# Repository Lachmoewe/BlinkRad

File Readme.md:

# BlinkRad

Using old or broken bicycle rims as an ilumination project.

36 boards, 36 rgb-LEDs, 36 attiny13, 108 FETs, 108 resistors 
(at least if youve got 36 spoke rims).
1 controller of your choice.

## Current Status

Got the current version (as of this commit) of boards at home.
Already got one working with 24bit RGB PWM. Now Im trying
to build a useful and robust data protocol. I was thinking
about sending packages with 4bit per color, a used bit and a 
sync bit, adding up to 14bit packages.

## Further plans
- network control with teensy3.1
- develop a protocol to send to attinys
- maybe 433MHz control
- you name it!

## Getting the code to work
You will need the following packages:
```
sudo apt-get install avr-libc binutils-avr gcc-avr avrdude libusb-dev
```

## Pretty Pictures

## Notes
If you want to edit the board, go with either Cadsoft Eagle or
edit the .brd files manually, its only xml.

Thanks to apmorton for creating the teensy template:
https://github.com/apmorton/teensy-template

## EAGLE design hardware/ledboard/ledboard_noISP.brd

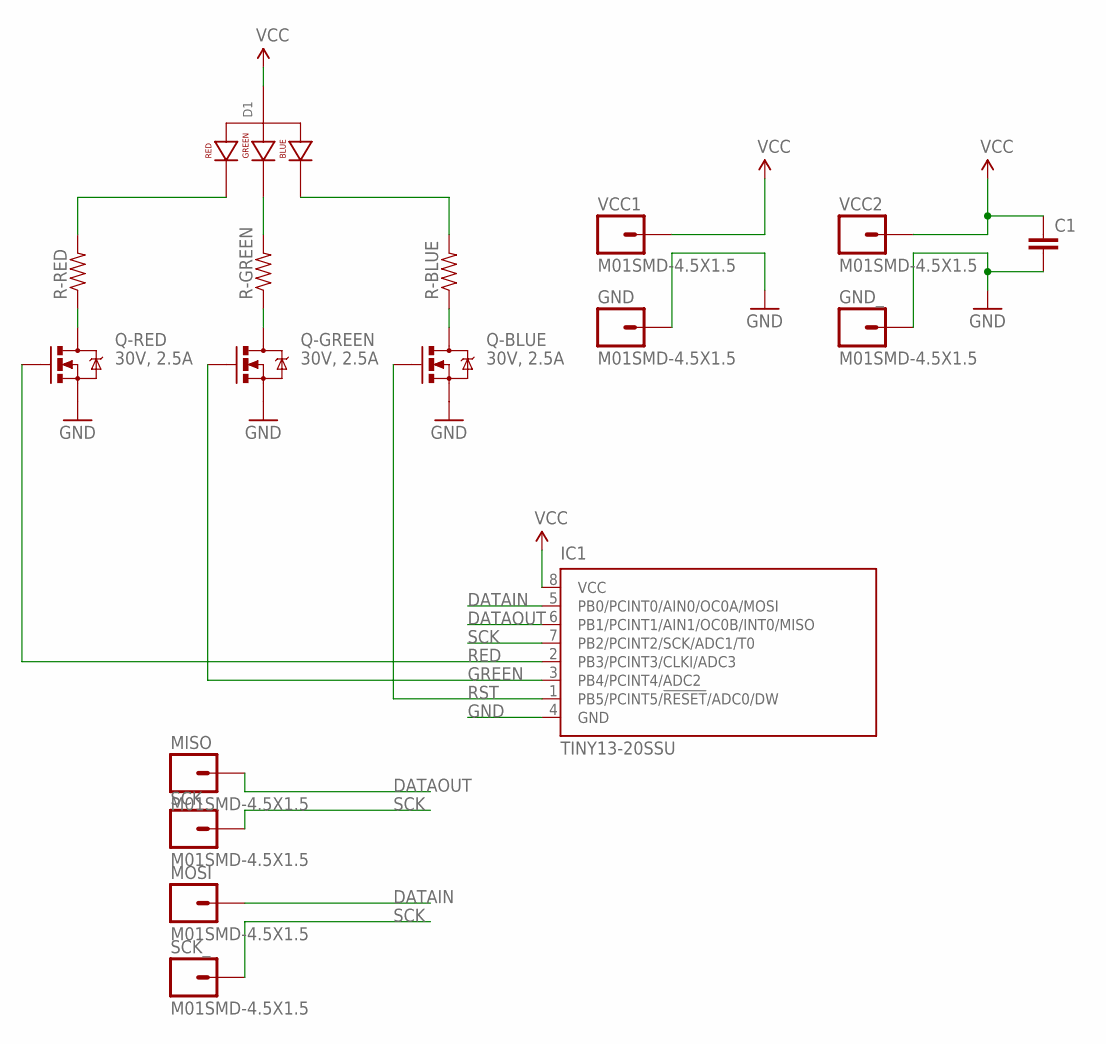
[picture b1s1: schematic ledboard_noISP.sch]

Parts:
C1: CAP0805; 0805
D1: LED-RGB-CA-THRUCLEAR; LED-RGB-THRU
GND: M01SMD-4.5X1.5; PAD-1.5X4.5
GND_: M01SMD-4.5X1.5; PAD-1.5X4.5
IC1: TINY13-20SSU; 8S1
MISO: M01SMD-4.5X1.5; PAD-1.5X4.5
MOSI: M01SMD-4.5X1.5; PAD-1.5X4.5
Q-BLUE: 30V, 2.5A; SOT23
Q-GREEN: 30V, 2.5A; SOT23
Q-RED: 30V, 2.5A; SOT23
R-BLUE: RESISTOR0603; 0603-RES
R-GREEN: RESISTOR0603; 0603-RES
R-RED: RESISTOR0603; 0603-RES
SCK: M01SMD-4.5X1.5; PAD-1.5X4.5
SCK_: M01SMD-4.5X1.5; PAD-1.5X4.5
VCC1, VCC2: M01SMD-4.5X1.5; PAD-1.5X4.5

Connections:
DATAIN: IC1.5 (PB0/PCINT0/AIN0/OC0A/MOSI), MOSI.P$1
DATAOUT: IC1.6 (PB1/PCINT1/AIN1/OC0B/INT0/MISO), MISO.P$1
GND: C1.2, GND.P$1, GND_.P$1, IC1.4 (GND), Q-BLUE.2 (S), Q-GREEN.2 (S), Q-RED.2 (S)
GREEN: IC1.3 (PB4/PCINT4/ADC2), Q-GREEN.1 (G)
unnamed: D1.1 (RED_CATHODE), R-RED.2
unnamed: Q-RED.3 (D), R-RED.1
unnamed: D1.4 (BLUE_CATHODE), R-BLUE.2
unnamed: D1.3 (GREEN_CATHODE), R-GREEN.2
unnamed: Q-GREEN.3 (D), R-GREEN.1
unnamed: Q-BLUE.3 (D), R-BLUE.1
RED: IC1.2 (PB3/PCINT3/CLKI/ADC3), Q-RED.1 (G)
RST: IC1.1 (PB5/PCINT5/!RESET!/ADC0/DW), Q-BLUE.1 (G)
SCK: IC1.7 (PB2/PCINT2/SCK/ADC1/T0), SCK.P$1, SCK_.P$1
VCC: C1.1, D1.2 (ANODE), IC1.8 (VCC), VCC1.P$1, VCC2.P$1

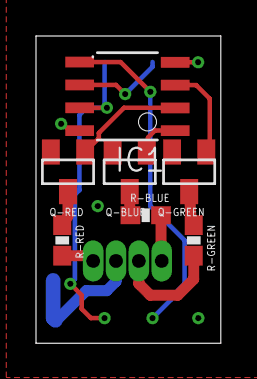
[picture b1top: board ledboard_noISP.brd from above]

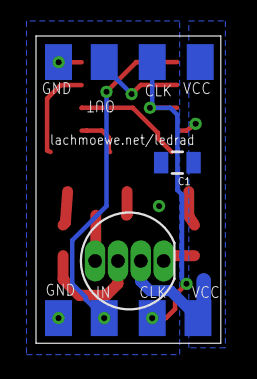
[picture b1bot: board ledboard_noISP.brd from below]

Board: 2 copper layers, 10.3 x 17.1 mm, 17 parts (10 on the bottom side), 14 nets.

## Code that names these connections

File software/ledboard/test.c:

#define F_CPU 8000000UL
#include <stdlib.h>
#include <avr/io.h>
#include <util/delay.h>
#include <stdint.h>

#define SCK     PB2
#define DATAIN  PB0
#define DATAOUT PB1
#define RED     PB3
#define GREEN   PB4
#define BLUE    PB5


const uint8_t lookup[16] = {
    0, 3, 7, 12, 19, 26, 35, 45, 58, 73, 91, 113, 140, 171, 209, 254
};

int PWM(uint8_t *color) {
    static uint8_t pwm_count = 0;
    if (pwm_count == 0) { PORTB |= (1<<RED)|(1<<GREEN)|(1<<BLUE); }
    if (pwm_count == *(color)  ) { PORTB &= ~(1<<RED); }
    if (pwm_count == *(color+1)) { PORTB &= ~(1<<GREEN); }
    if (pwm_count == *(color+2)) { PORTB &= ~(1<<BLUE); }
    
    pwm_count++;
}

void setColor(uint16_t cdata, uint8_t *color) {
    *(color)   = lookup[(cdata & 0x0F00)>>8];
    *(color+1) = lookup[(cdata & 0x00F0)>>4];
    *(color+2) = lookup[(cdata & 0x000F)];
}

int main(void) {

    DDRB = 0b00111010;
    // Set up Port B data to be all low
    PORTB = 0;  
    uint8_t color[3];
    uint8_t *colorptr = &color[0];
    uint16_t i=0x0880;
    uint16_t cdata = 0x0AA0;
    //setColor(0x0000, colorptr);
    *(colorptr)   = lookup[(i & 0x0F00)>>8];
    *(colorptr+1) = lookup[(i & 0x00F0)>>4];
    *(colorptr+2) = lookup[(i & 0x000F)];
    while (1) {
        uint16_t j=0;
        while (j<0x0fff) {
            //setColor(i, colorptr);
            
            //if (j = 10) { i++; }
            j++;
            PWM(colorptr);
            _delay_us(100);
        }
        uint8_t r,g,b;
        r = i>>8;
        g = i>>4;
        color[0] = lookup[(uint8_t)(r & 0x0F)];
        color[1] = lookup[(uint8_t)(g & 0x0F)];
        color[2] = lookup[(uint8_t)(i & 0xF)];
        i--;
    }
    return 0;
}

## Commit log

2014-08-10 MASSIVE ERROR, USE N FET
2014-08-10 added readme
2014-08-24 starting software
2014-08-25 fixing stuff
2014-10-13 working on communication
2014-10-13 status update
2014-10-13 instructions
2014-10-13 logic error
2014-10-13 communication code written, needs to be tested
2014-10-13 small counting error
2014-10-13 changes in folder hierarchy
2014-10-13 created media folder
2014-10-14 fixed error with used_oldstate
2014-10-14 added lookup table
2014-10-14 included teensy toolchain
2014-10-14 not about teensy-template
2014-10-14 folder structure changes
2014-10-15 now works out of the box
2014-10-15 made PB2 an output as it is required
2014-10-15 added some pictures
2014-10-15 testing pictures in readme
2014-10-15 added images to readme
2014-10-15 prettier readme
2014-10-15 added titles to readme pictures
2014-10-16 weird shit
2014-10-16 led now has all diodes fully on on startup
2014-10-17 fixed sync sequence
2014-10-22 named dataports
2014-10-22 added labels
2014-12-08 moving on with teensy code, so far nothing seems to work
2014-12-10 added ethercard
2014-12-10 deleted ethercard
2014-12-10 added uipethernet
2014-12-11 fiddling around, teensy does everything it should, ledboard doesnt
2014-12-11 prettyfied pwm
2014-12-11 fixed board fuckup
2014-12-11 forgot &
2014-12-11 renamed data in setcolor
2014-12-11 set usedbiton first free package to 1
2014-12-11 fixed bug with gotdata
2014-12-16 f***
2014-12-16 further

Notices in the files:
parts and their libraries:
SparkFun-LED: Licensing: Creative Commons ShareAlike 4.0 International - https://creativecommons.org/licenses/by-sa/4.0
